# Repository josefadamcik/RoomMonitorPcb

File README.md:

# RoomMonitorPcb

PCB design files (KiCad) for DYI room conditions monitor. 

- ESP8266 wifi connection & brain
- SHT21 - temperature and humidity sensor
- BH1750 - light intensity sensor.

All sesnors communicate via I2C bus. Data are sent to a MQTT broker.
¯

[A repository with firmware is also available on github.](https://github.com/josefadamcik/RoomMonitor)

More information can be found in this series of blog posts:

- [ESP8266 based room-conditions monitor, Part 1](https://josef-adamcik.cz/electronics/esp8266-based-room-conditions-monitor-part-1.html)
- [ESP8266 based room-conditions monitor, part 2: PCB](https://josef-adamcik.cz/electronics/esp8266-based-room-conditions-monitor-part-2.html)

There is also another project for a remote MQTT display for measured data:

- [Github project RoomMonitorClient](https://github.com/josefadamcik/RoomMonitorClient)
- blog post [Freeform ESP8266 OLED MQTT client](https://josef-adamcik.cz/electronics/freeform-esp8266-based-mqtt-oled-client.html)

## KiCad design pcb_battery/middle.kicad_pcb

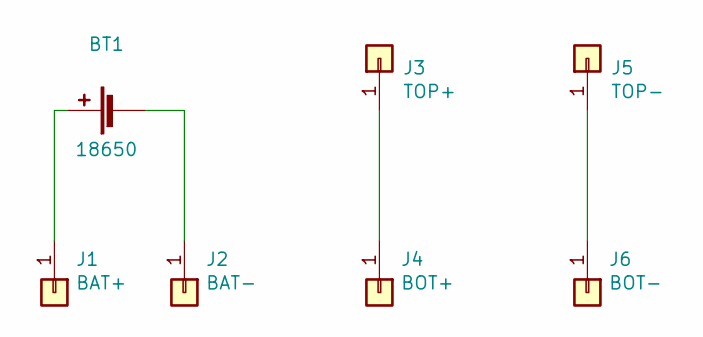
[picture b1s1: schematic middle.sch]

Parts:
BT1: 18650; BatteryHolder_MPD_BH-18650-PC2
J1: BAT+; SolderWirePad_1x01_Drill0.8mm
J2: BAT-; SolderWirePad_1x01_Drill0.8mm
J3: TOP+; SolderWirePad_1x01_Drill0.8mm
J4: BOT+; SolderWirePad_1x01_Drill0.8mm
J5: TOP-; SolderWirePad_1x01_Drill0.8mm
J6: BOT-; SolderWirePad_1x01_Drill0.8mm

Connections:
unnamed: BT1.1 (+), J1.1
unnamed: BT1.2 (-), J2.1
unnamed: J3.1, J4.1
unnamed: J5.1, J6.1

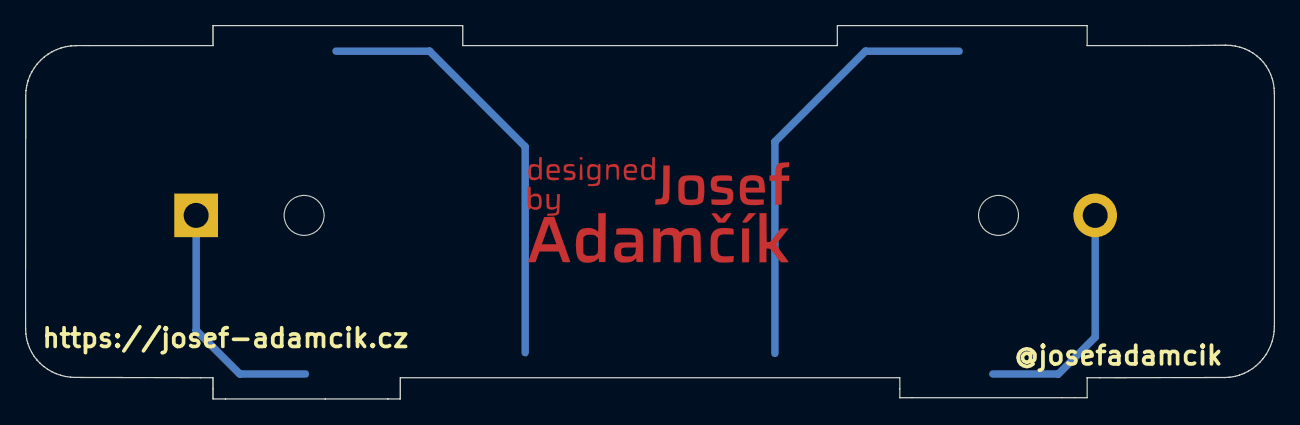
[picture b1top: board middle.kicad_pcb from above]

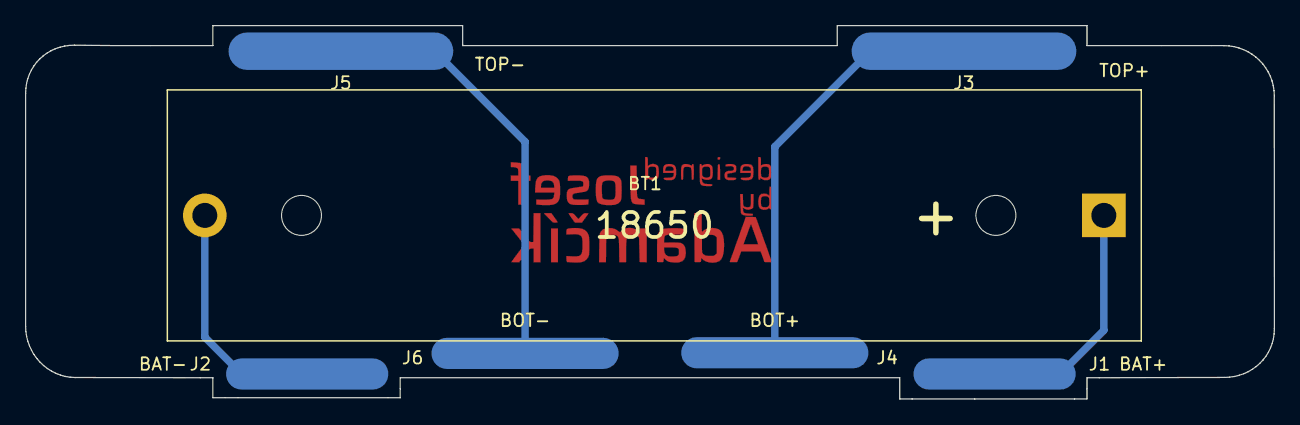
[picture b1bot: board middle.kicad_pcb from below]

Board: 2 copper layers, 100.0 x 29.9 mm, 8 parts (7 on the bottom side), 4 nets.

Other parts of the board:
Ref**: Val**; josef_adamcik_20mm_cu_mask

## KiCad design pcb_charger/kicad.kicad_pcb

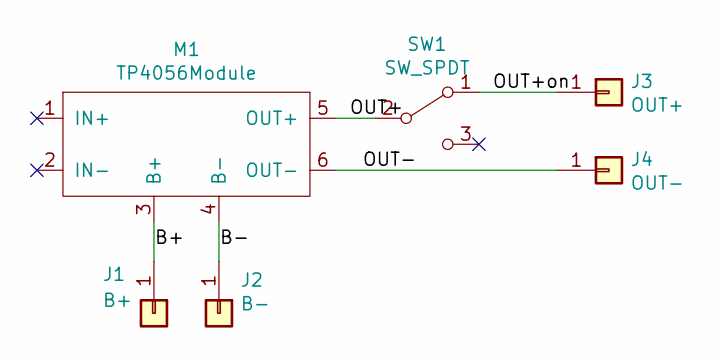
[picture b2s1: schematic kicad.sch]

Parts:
J1: B+; SolderWirePad_1x01_Drill0.8mm
J2: B-; SolderWirePad_1x01_Drill0.8mm
J3: OUT+; SolderWirePad_1x01_Drill0.8mm
J4: OUT-; SolderWirePad_1x01_Drill0.8mm
M1: TP4056Module; TP4056_Module
SW1: SW_SPDT; SW_SPDT_PCM12

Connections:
/B+: J1.1, M1.3 (B+)
/B-: J2.1, M1.4 (B-)
/OUT+: M1.5 (OUT+), SW1.2 (B)
/OUT+on: J3.1, SW1.1 (A)
/OUT-: J4.1, M1.6 (OUT-)

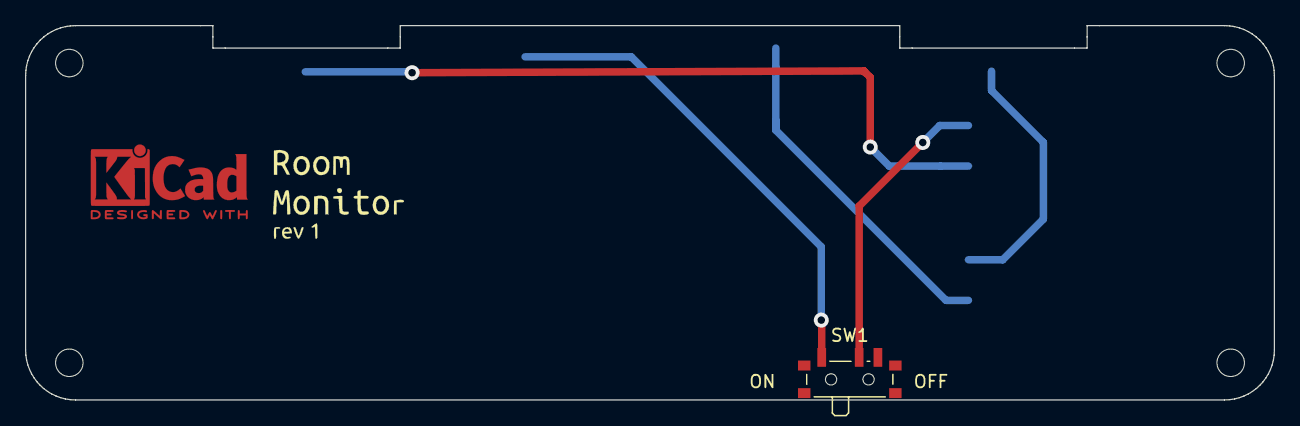
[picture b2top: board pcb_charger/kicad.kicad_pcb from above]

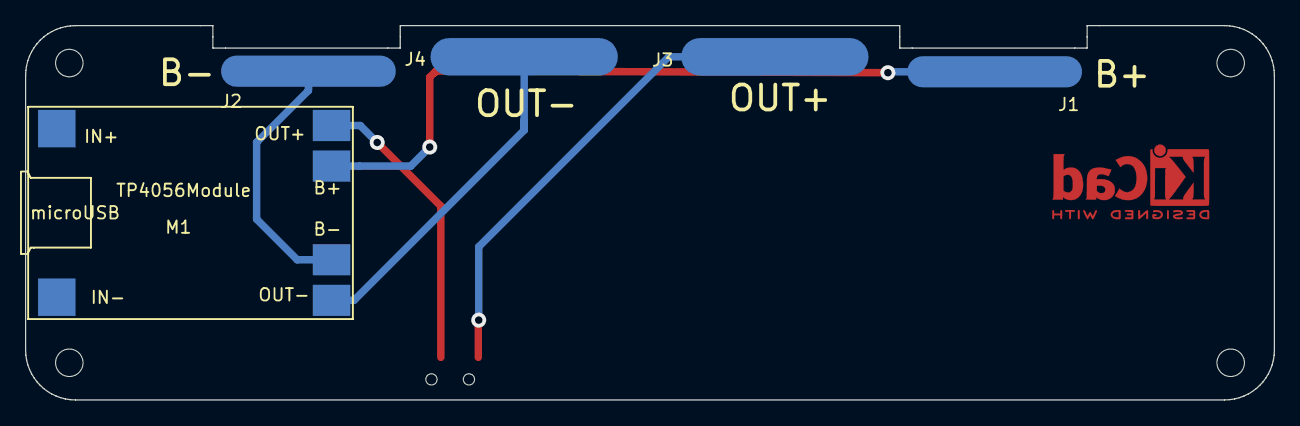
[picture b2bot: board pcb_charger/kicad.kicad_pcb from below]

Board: 2 copper layers, 100.0 x 30.0 mm, 7 parts (5 on the bottom side), 5 nets.

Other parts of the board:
Ref**: Val**; roommonitor-rev

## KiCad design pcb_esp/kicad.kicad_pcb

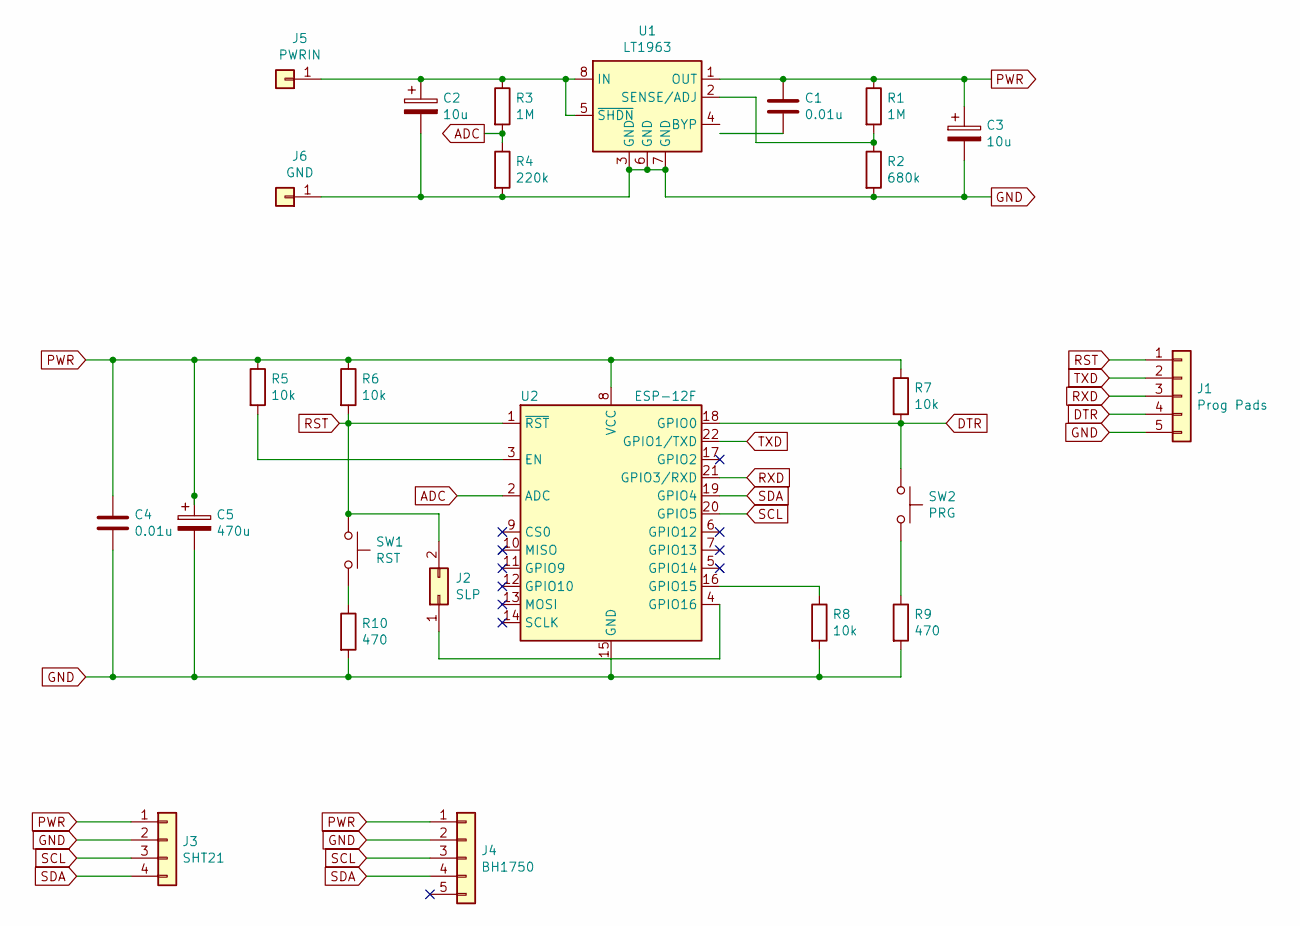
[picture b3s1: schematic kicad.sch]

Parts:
C1, C4: 0.01u; C_1206_3216Metric_Pad1.42x1.75mm_HandSolder
C2, C3: 10u; CP_Radial_D5.0mm_P2.50mm
C5: 470u; CP_Radial_D5.0mm_P2.50mm
J1: Prog Pads; PinHeader_1x05_P2.54mm_Vertical
J2: SLP; PinHeader_1x02_P2.54mm_Vertical
J3: SHT21; PinSocket_1x04_P2.54mm_Vertical
J4: BH1750; PinSocket_1x05_P2.54mm_Vertical
J5: PWRIN; SolderWirePad_1x01_Drill1mm
J6: GND; SolderWirePad_1x01_Drill1mm
R1, R3: 1M; R_1206_3216Metric
R2: 680k; R_1206_3216Metric
R4: 220k; R_1206_3216Metric
R5, R6, R7, R8: 10k; R_1206_3216Metric
R9, R10: 470; R_1206_3216Metric
SW1: RST; SW_Push_SPST_NO_Alps_SKRK
SW2: PRG; SW_Push_SPST_NO_Alps_SKRK
U1: LT1963; SO-8_3.9x4.9mm_P1.27mm
U2: ESP-12F; ESP-12E

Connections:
/ADJ: R1.2, R2.1, U1.2 (SENSE/ADJ)
/BYP: C1.2, U1.4 (BYP)
/EN: R5.2, U2.3 (EN)
/GPIO15: R8.1, U2.16 (GPIO15)
/GPIO16: J2.1, U2.4 (GPIO16)
/PWR+: C2.1, J5.1, R3.1, U1.5 (~SHDN), U1.8 (IN)
ADC: R3.2, R4.1, U2.2 (ADC)
DTR: J1.4, R7.2, SW2.1, U2.18 (GPIO0)
GND: C2.2, C3.2, C4.2, C5.2, J1.5, J3.2, J4.2, J6.1, R2.2, R4.2, R8.2, R9.2, R10.2, U1.3 (GND), U1.6 (GND), U1.7 (GND), U2.15 (GND)
unnamed: R9.1, SW2.2
unnamed: R10.1, SW1.2
PWR: C1.1, C3.1, C4.1, C5.1, J3.1, J4.1, R1.1, R5.1, R6.1, R7.1, U1.1 (OUT), U2.8 (VCC)
RST: J1.1, J2.2, R6.2, SW1.1, U2.1 (~RST)
RXD: J1.3, U2.21 (GPIO3/RXD)
SCL: J3.3, J4.3, U2.20 (GPIO5)
SDA: J3.4, J4.4, U2.19 (GPIO4)
TXD: J1.2, U2.22 (GPIO1/TXD)

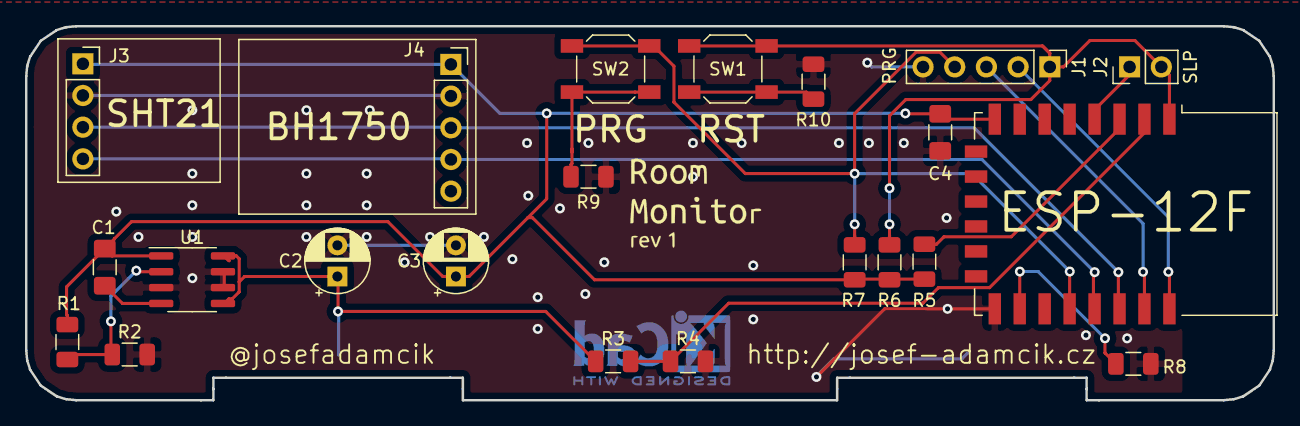
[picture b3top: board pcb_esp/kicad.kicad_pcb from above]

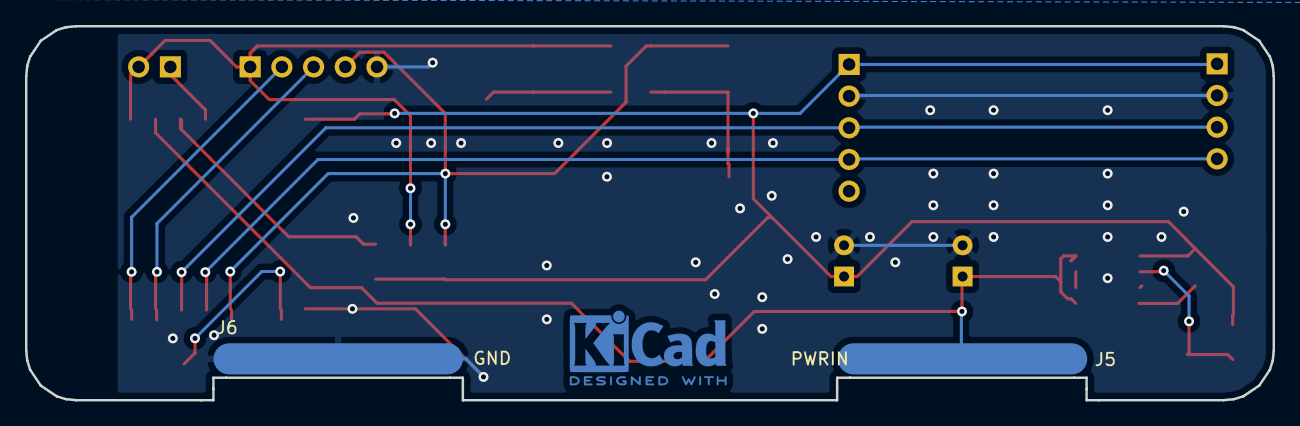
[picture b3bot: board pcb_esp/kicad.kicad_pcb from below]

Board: 2 copper layers, 100.0 x 30.0 mm, 25 parts (2 on the bottom side), 17 nets.

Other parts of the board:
Ref**: Val**; roommonitor-rev

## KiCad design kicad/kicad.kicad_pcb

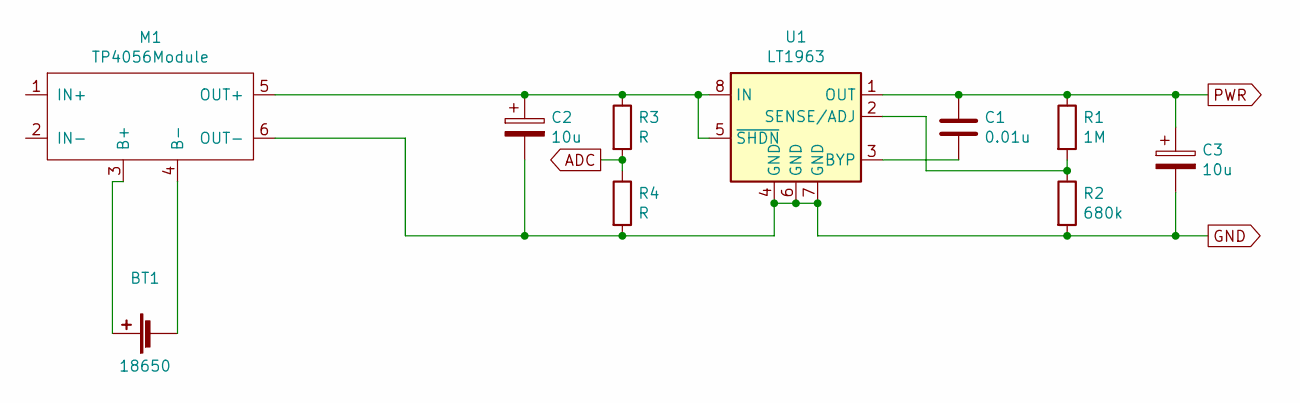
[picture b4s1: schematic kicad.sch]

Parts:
BT1: 18650; BatteryHolder_MPD_BH-18650-PC2
C1: 0.01u; C_1206_3216Metric_Pad1.42x1.75mm_HandSolder
C2, C3: 10u; CP_Radial_D5.0mm_P2.50mm
M1: TP4056Module; TP4056_Module
R1: 1M; R_1206_3216Metric
R2: 680k; R_1206_3216Metric
R3, R4: R; R_1206_3216Metric
U1: LT1963; SO-8_3.9x4.9mm_P1.27mm

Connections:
ADC: R3.2, R4.1
unnamed: BT1.1 (+), M1.3 (B+)
unnamed: BT1.2 (-), M1.4 (B-)
unnamed: C1.1, C3.1, R1.1, U1.1 (OUT)
unnamed: C1.2, U1.3 (BYP)
unnamed: C2.1, M1.5 (OUT+), R3.1, U1.5 (~SHDN), U1.8 (IN)
unnamed: C2.2, C3.2, M1.6 (OUT-), R2.2, R4.2, U1.4 (GND), U1.6 (GND), U1.7 (GND)
unnamed: R1.2, R2.1, U1.2 (SENSE/ADJ)

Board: 2 copper layers, 10 parts (0 on the bottom side), 8 nets, no tracks yet.

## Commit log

2019-08-28 Add epmty kicad project
2019-08-28 Symbol for LT1763, power schematic
2019-08-28 Footprints and symbols for charger, updated schematic.
2019-09-04 Rename project
2019-09-04 Copy to second project
2019-09-04 WIP first board for ESP and regulator
2019-09-05 Edge layer for to pcb, making it smaller (30 wide)
2019-09-05 Add pads for power contacts and main mechanical connection
2019-09-07 ESP module - placed and connected
2019-09-07 Change button footprint, ad kicad logo.
2019-09-07 Small, mostly visual, improvements
2019-09-08 Add firs draft of the middle (battery) pcb
2019-09-08 Add the bottom pcb.
2019-09-08 All 3 parts done
2019-09-08 Add GND connecting vias to the main PCB
2019-09-08 Few more small improvements.
2019-09-15 Fix lt1763 symbol (swapped gnd and byp pins) and fix pcb
2019-09-15 Gerber zip update
2019-09-15 Last changes to the charger board and gerbers
2019-12-10 Organise files a bit
2020-01-09 Update README.md
    Add more information, links to firmware and articles.
2020-03-01 Update trace and via sizes for battery and charger
